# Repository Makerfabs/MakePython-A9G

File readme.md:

# MakePython A9G

```c++
/*
Version:		V1.1
Author:			Vincent
Create Date:	2020/7/24
Note:
	20223/1/31		V1.1: Add Arduino example for AT Command test.
*/
```

[toc]

# Introduce

MakePython A9G is an IOT for GPRS / GSM + GPS module, users can use MicroPython to program it, which is very easy, especially for non-programmers. There is also a user guide to learn how to use the board to create the first IOT project, which allows beginners to quickly learn hardware and programming skills.

With this board, you will easy to add text, SMS and data to your project. It is good for your smart home project or GPS tracker and so on.

- You can get one from: [MakePython A9G](https://www.makerfabs.com/makepython-a9g-gprs-gps-shield.html)

- Hardware and detailed instructions please visit Wiki page: [MakePython A9G Wiki](https://wiki.makerfabs.com/MaESP_A9G.html)

# Related Test

Visit the wiki for details.

- Shows the GPS location on OLED display

- Display SMS message on OLED display

# Arduino Example

## at_command.ino

The AT instruction of serial port monitor can be forwarded to the A9G module.

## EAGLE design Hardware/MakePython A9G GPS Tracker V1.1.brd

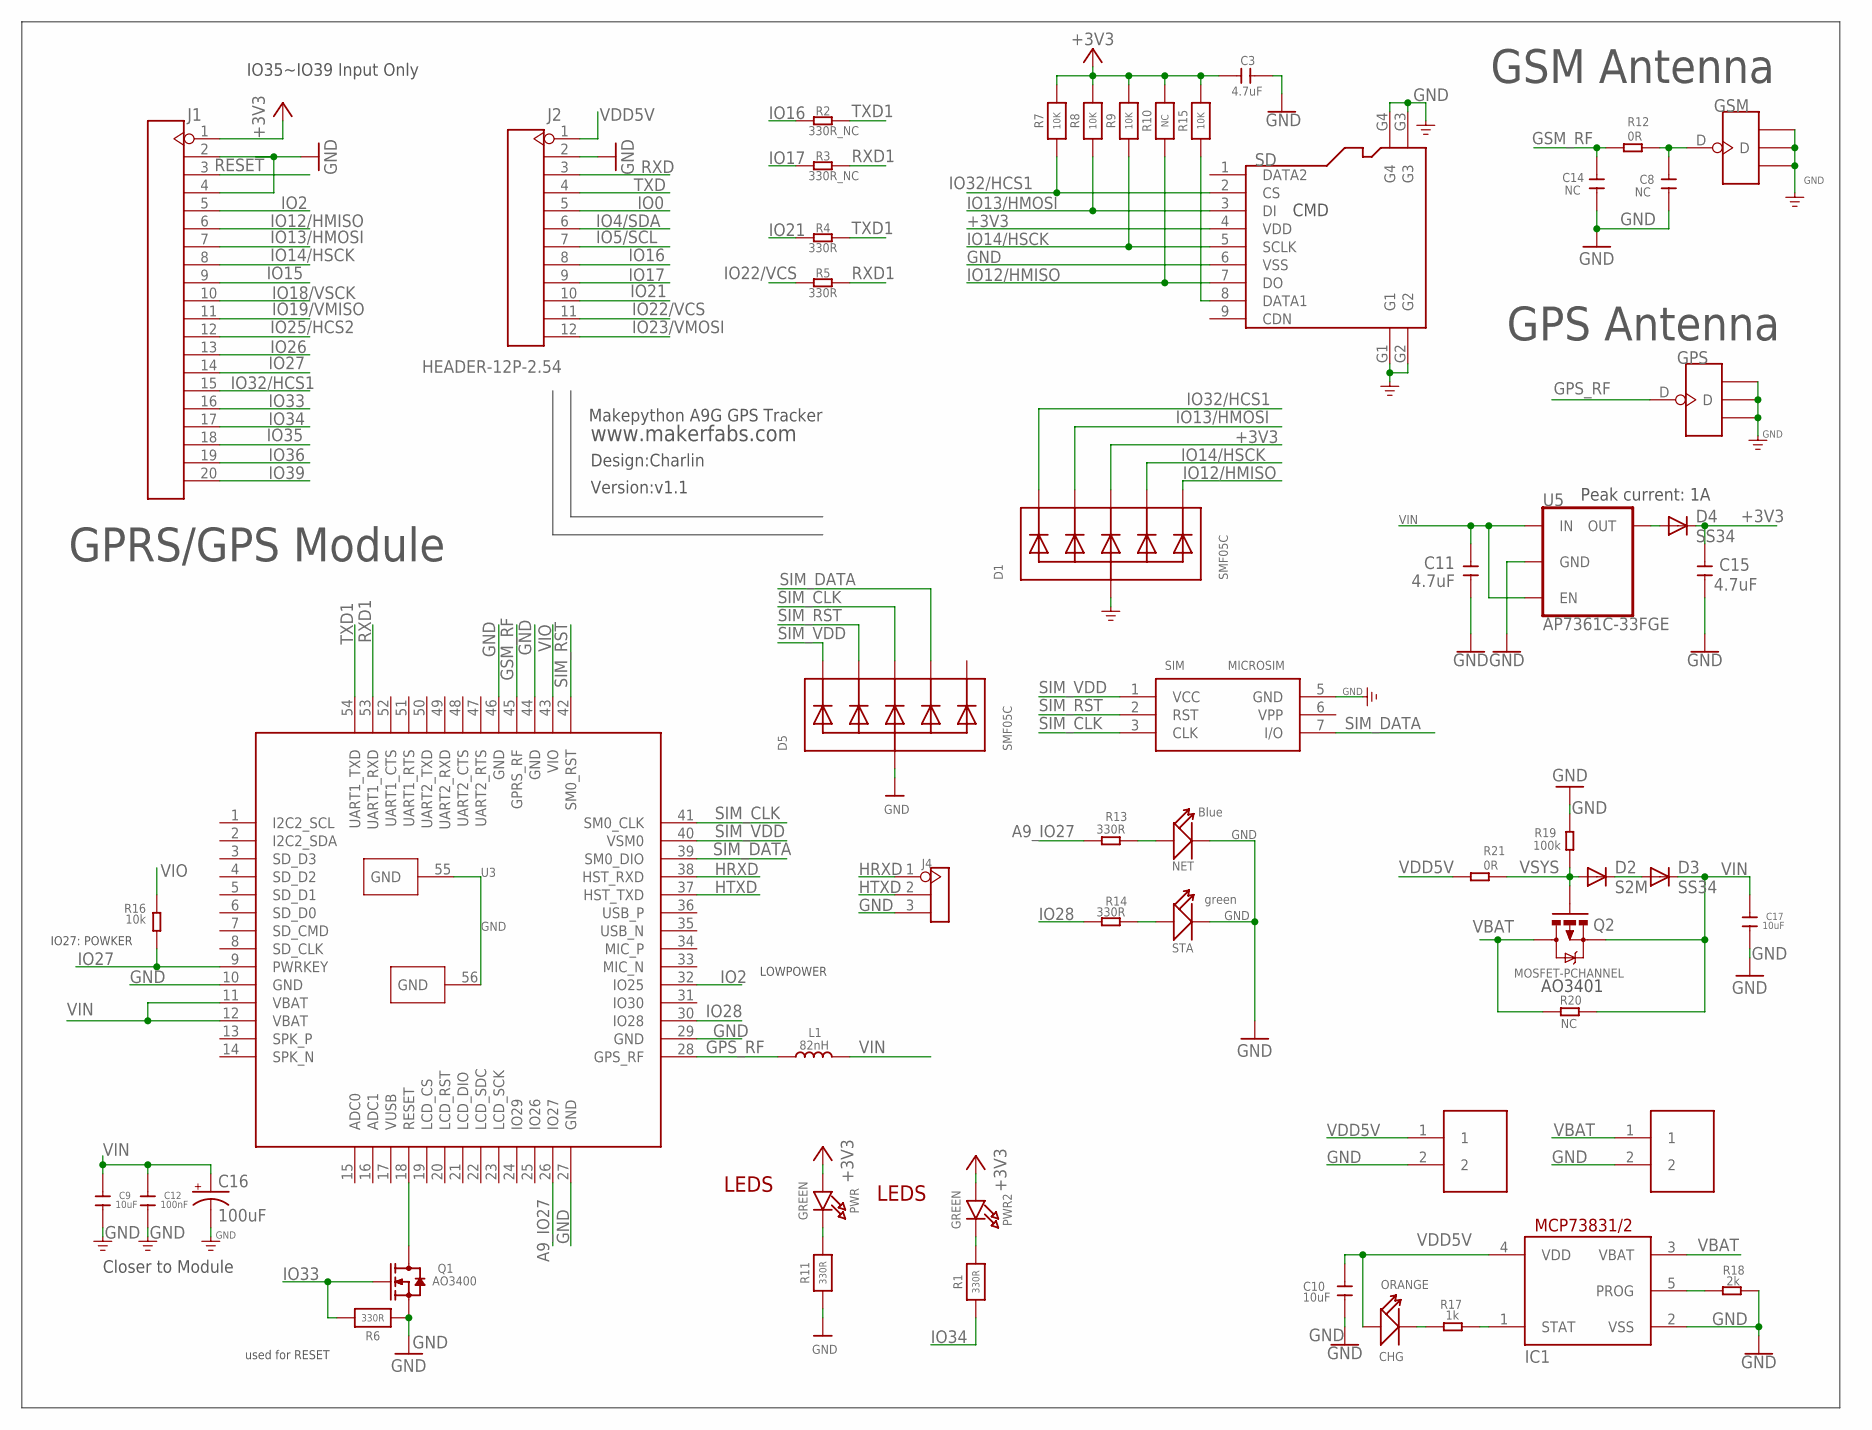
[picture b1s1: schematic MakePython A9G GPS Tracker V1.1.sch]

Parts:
BAT: PH2.0-2P-90-DIP
C3: 4.7uF; DISCRETE_C0603
C8, C14: NC; C0402
C9, C10, C17: 10uF; C0603
C11, C15: 4.7uF; C0603
C12: 100nF; C0603
C16: 100uF; EIA3528
CHG: ORANGE; D0603
CHRG: PH2.0-2P-90-DIP
D1, D5: SMF05C; SOT363
D2: S2M; DO-214AC
D3, D4: SS34; DO-214AC
GPS: ANTENNA-U-FL; 4P-U-FL
GSM: ANTENNA-U-FL; 4P-U-FL
IC1: MCP73831/OT; SOT23-5L
J1: HEADER-20P-2.54; 20P-2.54
J2: HEADER-12P-2.54; 12P-2.54
J4: HEADER-3P-2.54; 3P-2.54
L1: 82nH; L0603
NET: Blue; LED-0603
PWR, PWR2: GREEN; CHIPLED_0805_NOOUTLINE
Q1: AO3400; SOT23@1
Q2: MOSFET-PCHANNEL; SOT23-3
R1, R6, R11: 330R; 0603-NO
R2, R3: 330R_NC; R0603
R4, R5, R13, R14: 330R; R0603
R7, R8, R9, R15: 10K; 0603-NO
R10: NC; 0603-NO
R12, R21: 0R; R0603
R16: 10k; R0603
R17: 1k; R0603
R18: 2k; R0603
R19: 100k; R0603
R20: NC; R0603
SD: HOLDER-MICROSD-9P; 9P-SMD-W/-RING
SIM: MICROSIM
STA: green; LED-0603
U3: A9G
U5: AP7361C-33FGE; 8-UDFN

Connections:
+3V3: C3.2, C15.2, D1.4 (C3), D4.C, J1.1, PWR.A, PWR2.A, R7.2, R8.2, R9.2, R10.2, R15.2, SD.4 (VDD)
A9_IO27: R13.1, U3.26 (IO27)
GND: BAT.2, C3.1, C8.1, C9.1, C10.1, C11.1, C12.1, C14.1, C15.1, C16.C (-), C17.1, CHRG.2, D1.2 (A), D5.2 (A), GPS.GND1, GPS.GND2, GPS.GND3, GSM.GND1, GSM.GND2, GSM.GND3, IC1.2 (VSS), J1.2, J1.4, J2.2, J4.3, NET.-, Q1.2 (S), R6.1, R11.1, R18.2, R19.2, SD.6 (VSS), SD.G1, SD.G2, SD.G3, SD.G4, SIM.5 (GND), STA.-, U3.10 (GND), U3.27 (GND), U3.29 (GND), U3.44 (GND), U3.46 (GND), U3.55 (GND), U3.56 (GND), U5.4 (GND), U5.EP (GND)
GPS_RF: GPS.D, L1.1, U3.28 (GPS_RF)
GSM_RF: C14.2, R12.1, U3.45 (GPRS_RF)
HRXD: J4.1, U3.38 (HST_RXD)
HTXD: J4.2, U3.37 (HST_TXD)
IO0: J2.5
IO2: J1.5, U3.32 (IO25)
IO4/SDA: J2.6, R15.1, SD.8 (DATA1)
IO5/SCL: J2.7
IO12/HMISO: D1.6 (C5), J1.6, R10.1, SD.7 (DO)
IO13/HMOSI: D1.3 (C2), J1.7, R8.1, SD.3 (DI)
IO14/HSCK: D1.5 (C4), J1.8, R9.1, SD.5 (SCLK)
IO15: J1.9
IO16: J2.8, R2.1
IO17: J2.9, R3.1
IO18/VSCK: J1.10
IO19/VMISO: J1.11
IO21: J2.10, R4.1
IO22/VCS: J2.11, R5.1
IO23/VMOSI: J2.12
IO25/HCS2: J1.12
IO26: J1.13
IO27: J1.14, R16.1, U3.9 (PWRKEY)
IO28: R14.1, U3.30 (IO28)
IO32/HCS1: D1.1 (C1), J1.15, R7.1, SD.2 (CS)
IO33: J1.16, Q1.1 (G), R6.2
IO34: J1.17, R1.1
IO35: J1.18
IO36: J1.19
IO39: J1.20
unnamed: PWR2.C, R1.2
unnamed: D4.A, U5.1 (OUT)
unnamed: R14.2, STA.+
unnamed: PWR.C, R11.2
unnamed: D2.C, D3.A
unnamed: NET.+, R13.2
unnamed: Q1.3 (D), U3.18 (RESET)
unnamed: CHG.-, R17.1
unnamed: IC1.1 (STAT), R17.2
unnamed: IC1.5 (PROG), R18.1
unnamed: C8.2, GSM.D, R12.2
RESET: J1.3
RXD: J2.3
RXD1: R3.2, R5.2, U3.53 (UART1_RXD)
SIM_CLK: D5.4 (C3), SIM.3 (CLK), U3.41 (SM0_CLK)
SIM_DATA: D5.5 (C4), SIM.7 (I/O), U3.39 (SM0_DIO)
SIM_RST: D5.3 (C2), SIM.2 (RST), U3.42 (SM0_RST)
SIM_VDD: D5.1 (C1), SIM.1 (VCC), U3.40 (VSM0)
TXD: J2.4
TXD1: R2.2, R4.2, U3.54 (UART1_TXD)
VBAT: BAT.1, IC1.3 (VBAT), Q2.3 (D), R20.1
VDD5V: C10.2, CHG.+, CHRG.1, IC1.4 (VDD), J2.1, R21.1
VIN: C9.2, C11.2, C12.2, C16.A (+), C17.2, D3.C, L1.2, Q2.2 (S), R20.2, U3.11 (VBAT), U3.12 (VBAT), U5.5 (EN), U5.8 (IN)
VIO: R16.2, U3.43 (VIO)
VSYS: D2.A, Q2.1 (G), R19.1, R21.2

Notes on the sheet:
IO35~IO39 Input Only
Makepython A9G GPS Tracker
LEDS
GSM Antenna
GPS Antenna
GPRS/GPS Module
LOWPOWER
used for RESET
IO27: POWKER
www.makerfabs.com
Design:Charlin
Closer to Module
Version:v1.1
AO3401
Peak current: 1A
CMD

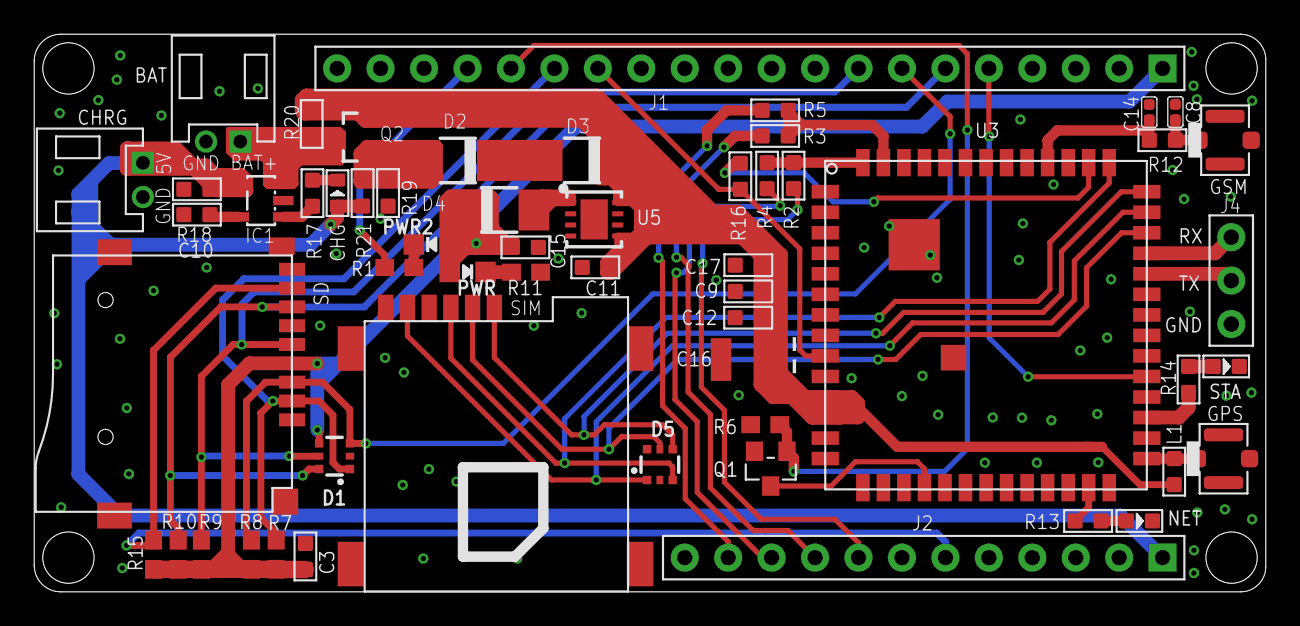
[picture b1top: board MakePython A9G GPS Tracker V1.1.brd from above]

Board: 2 copper layers, 72.0 x 32.6 mm, 57 parts (1 on the bottom side), 43 nets.

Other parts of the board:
U$1: MAKERFABS_0.3

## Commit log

2020-07-24 put py to workSpace
2021-02-25 creat
2021-03-03 create
2021-07-17 Makepython A9G AT cammand test
2023-01-31 V1.1 Add arduino example

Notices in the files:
parts and their libraries:
microbuilder: This work is placed in the public domain, and may be freely used for commercial and non-commercial work with the following conditions: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
SparkFun-Capacitors: Licensing: Creative Commons ShareAlike 4.0 International - https://creativecommons.org/licenses/by-sa/4.0
